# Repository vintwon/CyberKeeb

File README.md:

# CyberKeeb

## Some info...
This started as boredom, and evolved into my second keyboard! The theme came from some inspiration I saw from another keyboard on reddit, so I decided to do something similar. I wanted to use a rpi pico w but I didn't want to have extra space at the edge of the board, so I decided to make a daughterboard type situation. 
There are holes here: 

The traces are connected to the holes on the board which will then be connected to the rpi pico w which is mounted here using wires:

This way the usb-c port is centered in the back of the board and It gives me room to make the centerpiece of the keyboard:

Oh! And here is the pcb!

I went with a green and black theme simply because those are the colors of filament I have available right now. The geometrically interesting features are layerd, with each color on a different layer to provide depth. 
**ALSO QMK IS BEING USED YAYYY**

## BOM
!!! WARNING: ALIEXPRESS PRICES ARE VOLATILE AND SUBJECT TO CHAGE !!!

| Item                      | Link                                                                                                                                                                                                                                                              | Price(USD)               | Notes                                                                                              |
|---------------------------|-------------------------------------------------------------------------------------------------------------------------------------------------------------------------------------------------------------------------------------------------------------------|--------------------------|----------------------------------------------------------------------------------------------------|
|                           |                                                                                                                                                                                                                                                                   |                          |                                                                                                    |
| PCB                       | you must order the pcb yourself through your preferred pcb manufacturer.                                                                                                                                                                                          | ~$32 with shipping       | Shipping and import taxes vary, for me it costs $32 on jlcpcb, which is the cheapest I could find. |
| KTT Kang White Switches   | https://www.aliexpress.com/item/3256806762410255.html?spm=a2g0o.detail.0.0.6c77geBPgeBPyV&mp=1&pdp_npi=6%40dis%21USD%21USD%2012.15%21USD%2010.15%21%21USD%2010.15%21%21%21%40210337c117782580279017048e1338%2112000038824233347%21ct%21US%21-1%21%211%210%21      | $12.15 total             |                                                                                                    |
| DO-35 1N4148 diodes       | https://www.aliexpress.com/item/3256811531564621.html?spm=a2g0o.detail.0.0.68d0o71qo71qjR&mp=1&pdp_npi=6%40dis%21USD%21USD%207.18%21USD%203.59%21%21USD%203.58%21%21%21%4021030a4b17766365398052905e9466%2112000056337427991%21ct%21US%216216336952%21%211%210%21 | $2                       |                                                                                                    |
| Raspberry Pi Pico W       | https://www.aliexpress.com/item/3256811531564621.html?spm=a2g0o.detail.0.0.6f1fVbwRVbwR5M&mp=1&pdp_npi=6%40dis%21USD%21USD%207.18%21USD%203.59%21%21USD%203.58%21%21%21%4021030a4b17766366052814234e9466%2112000056337427991%21ct%21US%216216336952%21%211%210%21 | $2                       |                                                                                                    |
| DUROCK stabilizers        | https://www.aliexpress.com/item/3256806342416791.html?spm=a2g0o.detail.0.0.1bfaZBZ3ZBZ3Vb&mp=1&pdp_npi=6%40dis%21USD%21USD%206.95%21USD%203.85%21%21USD%203.85%21%21%21%4021030a4b17766366461885220e9466%2112000037543723481%21ct%21US%216216336952%21%211%210%21 | $3.85                    |                                                                                                    |
| Lubricant                 | https://www.aliexpress.com/item/3256803007713392.html?spm=a2g0o.detail.0.0.4527bQDebQDeh5&mp=1&pdp_npi=6%40dis%21USD%21USD%209.67%21USD%209.67%21%21USD%209.52%21%21%21%40210337c117782586996374657e1338%2112000024598551823%21ct%21US%216216336952%21%212%210%21 | $9.67(for one)           | Buy two                                                                                            |
|                           |                                                                                                                                                                                                                                                                   |                          |                                                                                                    |
| Total                     |                                                                                                                                                                                                                                                                   | $71.34                   | ALIEXPRESS PRICES ARE VOLATILE!!!!                                                                 |

### <a href="https://cad.onshape.com/documents/5317cbb2be7b5bc0767f3a0c/">CAD in onshape :3</a>

## Zine!!!

## Build instructions coming soon!

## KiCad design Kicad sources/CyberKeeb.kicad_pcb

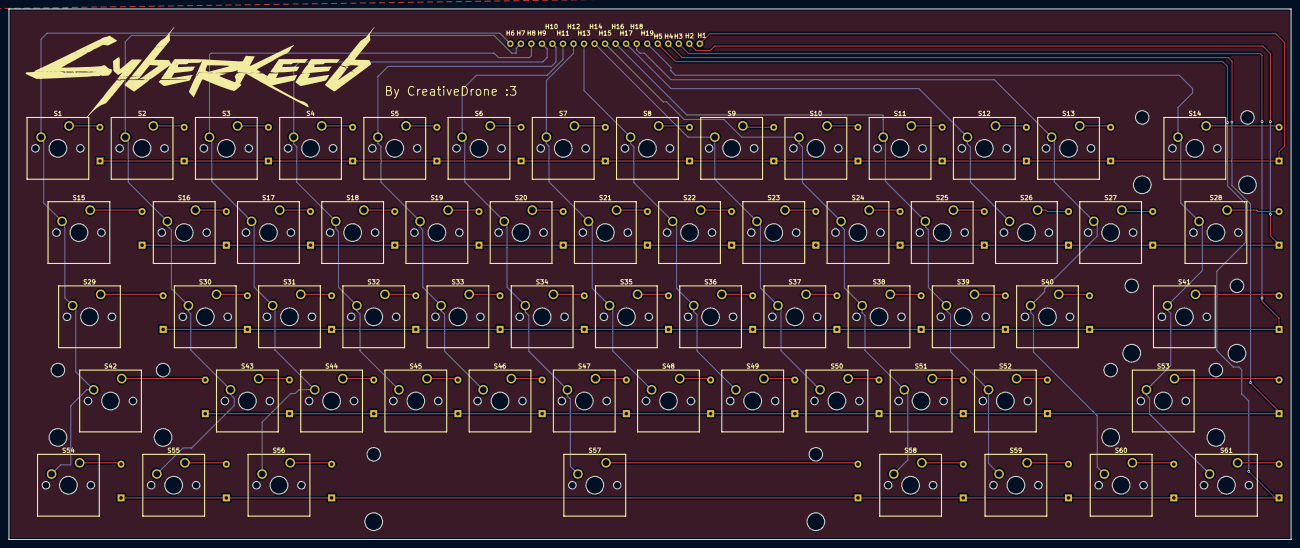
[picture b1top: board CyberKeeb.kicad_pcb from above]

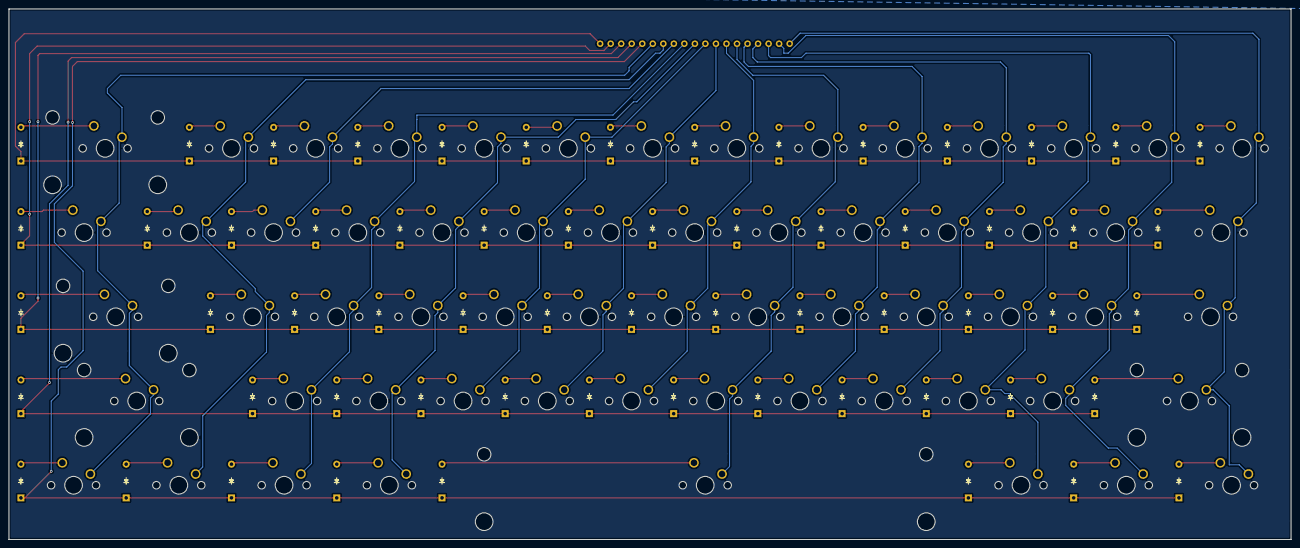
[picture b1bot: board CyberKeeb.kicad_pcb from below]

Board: 2 copper layers, 290.0 x 120.0 mm, 141 parts (61 on the bottom side), 80 nets.

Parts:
D1, D2, D3, D4, D5, D6, D7, D8, D9, D10, D11, D12, D13, D14, D15, D16, D17, D18, D19, D20, D21, D22, D23, D24, D25, D26, D27, D28, D29, D30, D31, D32, D33, D34, D35, D36, D37, D38, D39, D40, D41, D42, D43, D44, D45, D46, D47, D48, D49, D50, D51, D52, D53, D54, D55, D56, D57, D58, D59, D60, D61: Diode_DO-35
H1, H3, H4, H5, H6, H7, H8, H9, H10, H11, H12, H13, H14, H15, H16, H17, H18, H19: MountingHole_M3_3.2mm_Pad; CPH
H2: CPH
S1, S2, S3, S4, S5, S6, S7, S8, S9, S10, S11, S12, S13, S16, S17, S18, S19, S20, S21, S22, S23, S24, S25, S26, S27, S30, S31, S32, S33, S34, S35, S36, S37, S38, S39, S40, S43, S44, S45, S46, S47, S48, S49, S50, S51, S52: SW_Cherry_MX_1.00u_PCB
S14: SW_Cherry_MX_2.00u_PCB
S15, S28: SW_Cherry_MX_1.50u_PCB
S29: SW_Cherry_MX_1.75u_PCB
S41, S42: SW_Cherry_MX_2.25u_PCB
S53: SW_Cherry_MX_2.75u_PCB
S54, S55, S56, S58, S59, S60, S61: SW_Cherry_MX_1.25u_PCB
S57: SW_Cherry_MX_6.25u_PCB

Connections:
Column 0: H6.1, S1.2, S15.2, S29.2, S42.2, S54.2
Column 1: H7.1, S2.2, S16.2, S30.2, S43.2, S55.2
Column 2: H8.1, S3.2, S17.2, S31.2, S44.2, S56.2
Column 3: H9.1, S4.2, S18.2, S32.2, S45.2
Column 4: H10.1, S5.2, S19.2, S33.2, S46.2
Column 5: H11.1, S6.2, S20.2, S34.2, S47.2, S57.2
Column 6: H12.1, S7.2, S21.2, S35.2, S48.2
Column 7: H13.1, S8.2, S22.2, S36.2, S49.2
Column 8: H14.1, S9.2, S23.2, S37.2, S50.2
Column 9: H15.1, S10.2, S24.2, S38.2, S51.2, S58.2
Column 10: H16.1, S11.2, S25.2, S39.2, S52.2, S59.2
Column 11: H17.1, S12.2, S26.2
Column 12: H18.1, S13.2, S27.2, S40.2, S60.2
Column 13: H19.1, S14.2, S28.2, S41.2, S53.2, S61.2
unnamed: D1.2 (A), S1.1
unnamed: D2.2 (A), S2.1
unnamed: D3.2 (A), S3.1
unnamed: D4.2 (A), S4.1
unnamed: D5.2 (A), S5.1
unnamed: D6.2 (A), S6.1
unnamed: D7.2 (A), S7.1
unnamed: D8.2 (A), S8.1
unnamed: D9.2 (A), S9.1
unnamed: D10.2 (A), S10.1
unnamed: D11.2 (A), S11.1
unnamed: D12.2 (A), S12.1
unnamed: D13.2 (A), S13.1
unnamed: D14.2 (A), S14.1
unnamed: D15.2 (A), S15.1
unnamed: D16.2 (A), S16.1
unnamed: D17.2 (A), S17.1
unnamed: D18.2 (A), S18.1
unnamed: D19.2 (A), S19.1
unnamed: D20.2 (A), S20.1
unnamed: D21.2 (A), S21.1
unnamed: D22.2 (A), S22.1
unnamed: D23.2 (A), S23.1
unnamed: D24.2 (A), S24.1
unnamed: D25.2 (A), S25.1
unnamed: D26.2 (A), S26.1
unnamed: D27.2 (A), S27.1
unnamed: D28.2 (A), S28.1
unnamed: D29.2 (A), S29.1
unnamed: D30.2 (A), S30.1
unnamed: D31.2 (A), S31.1
unnamed: D32.2 (A), S32.1
unnamed: D33.2 (A), S33.1
unnamed: D34.2 (A), S34.1
unnamed: D35.2 (A), S35.1
unnamed: D36.2 (A), S36.1
unnamed: D37.2 (A), S37.1
unnamed: D38.2 (A), S38.1
unnamed: D39.2 (A), S39.1
unnamed: D40.2 (A), S40.1
unnamed: D41.2 (A), S41.1
unnamed: D42.2 (A), S42.1
unnamed: D43.2 (A), S43.1
unnamed: D44.2 (A), S44.1
unnamed: D45.2 (A), S45.1
unnamed: D46.2 (A), S46.1
unnamed: D47.2 (A), S47.1
unnamed: D48.2 (A), S48.1
unnamed: D49.2 (A), S49.1
unnamed: D50.2 (A), S50.1
unnamed: D51.2 (A), S51.1
unnamed: D52.2 (A), S52.1
unnamed: D53.2 (A), S53.1
unnamed: D54.2 (A), S54.1
unnamed: D55.2 (A), S55.1
unnamed: D56.2 (A), S56.1
unnamed: D57.2 (A), S57.1
unnamed: D58.2 (A), S58.1
unnamed: D59.2 (A), S59.1
unnamed: D60.2 (A), S60.1
unnamed: D61.2 (A), S61.1
Row 0: D1.1 (K), D2.1 (K), D3.1 (K), D4.1 (K), D5.1 (K), D6.1 (K), D7.1 (K), D8.1 (K), D9.1 (K), D10.1 (K), D11.1 (K), D12.1 (K), D13.1 (K), D14.1 (K), H1.1
Row 1: D15.1 (K), D16.1 (K), D17.1 (K), D18.1 (K), D19.1 (K), D20.1 (K), D21.1 (K), D22.1 (K), D23.1 (K), D24.1 (K), D25.1 (K), D26.1 (K), D27.1 (K), D28.1 (K), H2.1
Row 2: D29.1 (K), D30.1 (K), D31.1 (K), D32.1 (K), D33.1 (K), D34.1 (K), D35.1 (K), D36.1 (K), D37.1 (K), D38.1 (K), D39.1 (K), D40.1 (K), D41.1 (K), H3.1
Row 3: D42.1 (K), D43.1 (K), D44.1 (K), D45.1 (K), D46.1 (K), D47.1 (K), D48.1 (K), D49.1 (K), D50.1 (K), D51.1 (K), D52.1 (K), D53.1 (K), H4.1
Row 4: D54.1 (K), D55.1 (K), D56.1 (K), D57.1 (K), D58.1 (K), D59.1 (K), D60.1 (K), D61.1 (K), H5.1

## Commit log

2026-04-19 Expand README with project details and BOM
    Added detailed project information, BOM, and images.
2026-04-19 Fix README formatting and add PCB image
    Corrected formatting and added PCB image to README.
2026-04-19 Added kicad files
2026-04-19 added bom
2026-04-19 Add image to README for project visualization
    Added an image to the README for better visualization.
2026-04-19 Add build instructions section to README
    Added a section for upcoming build instructions.
2026-04-23 Add additional images to README
2026-04-23 Added zine
2026-04-23 asfsafsa
2026-04-23 Deleted broken zine
2026-04-23 Add Zine section with image to README
2026-04-23 Update README with VIA usage note
    Added a note about using VIA in the project.
2026-04-23 Added CAD and firmware files for the cyberkeeb keyboard project.
2026-04-23 QMK, not via
2026-05-08 Update component list and total cost in README
